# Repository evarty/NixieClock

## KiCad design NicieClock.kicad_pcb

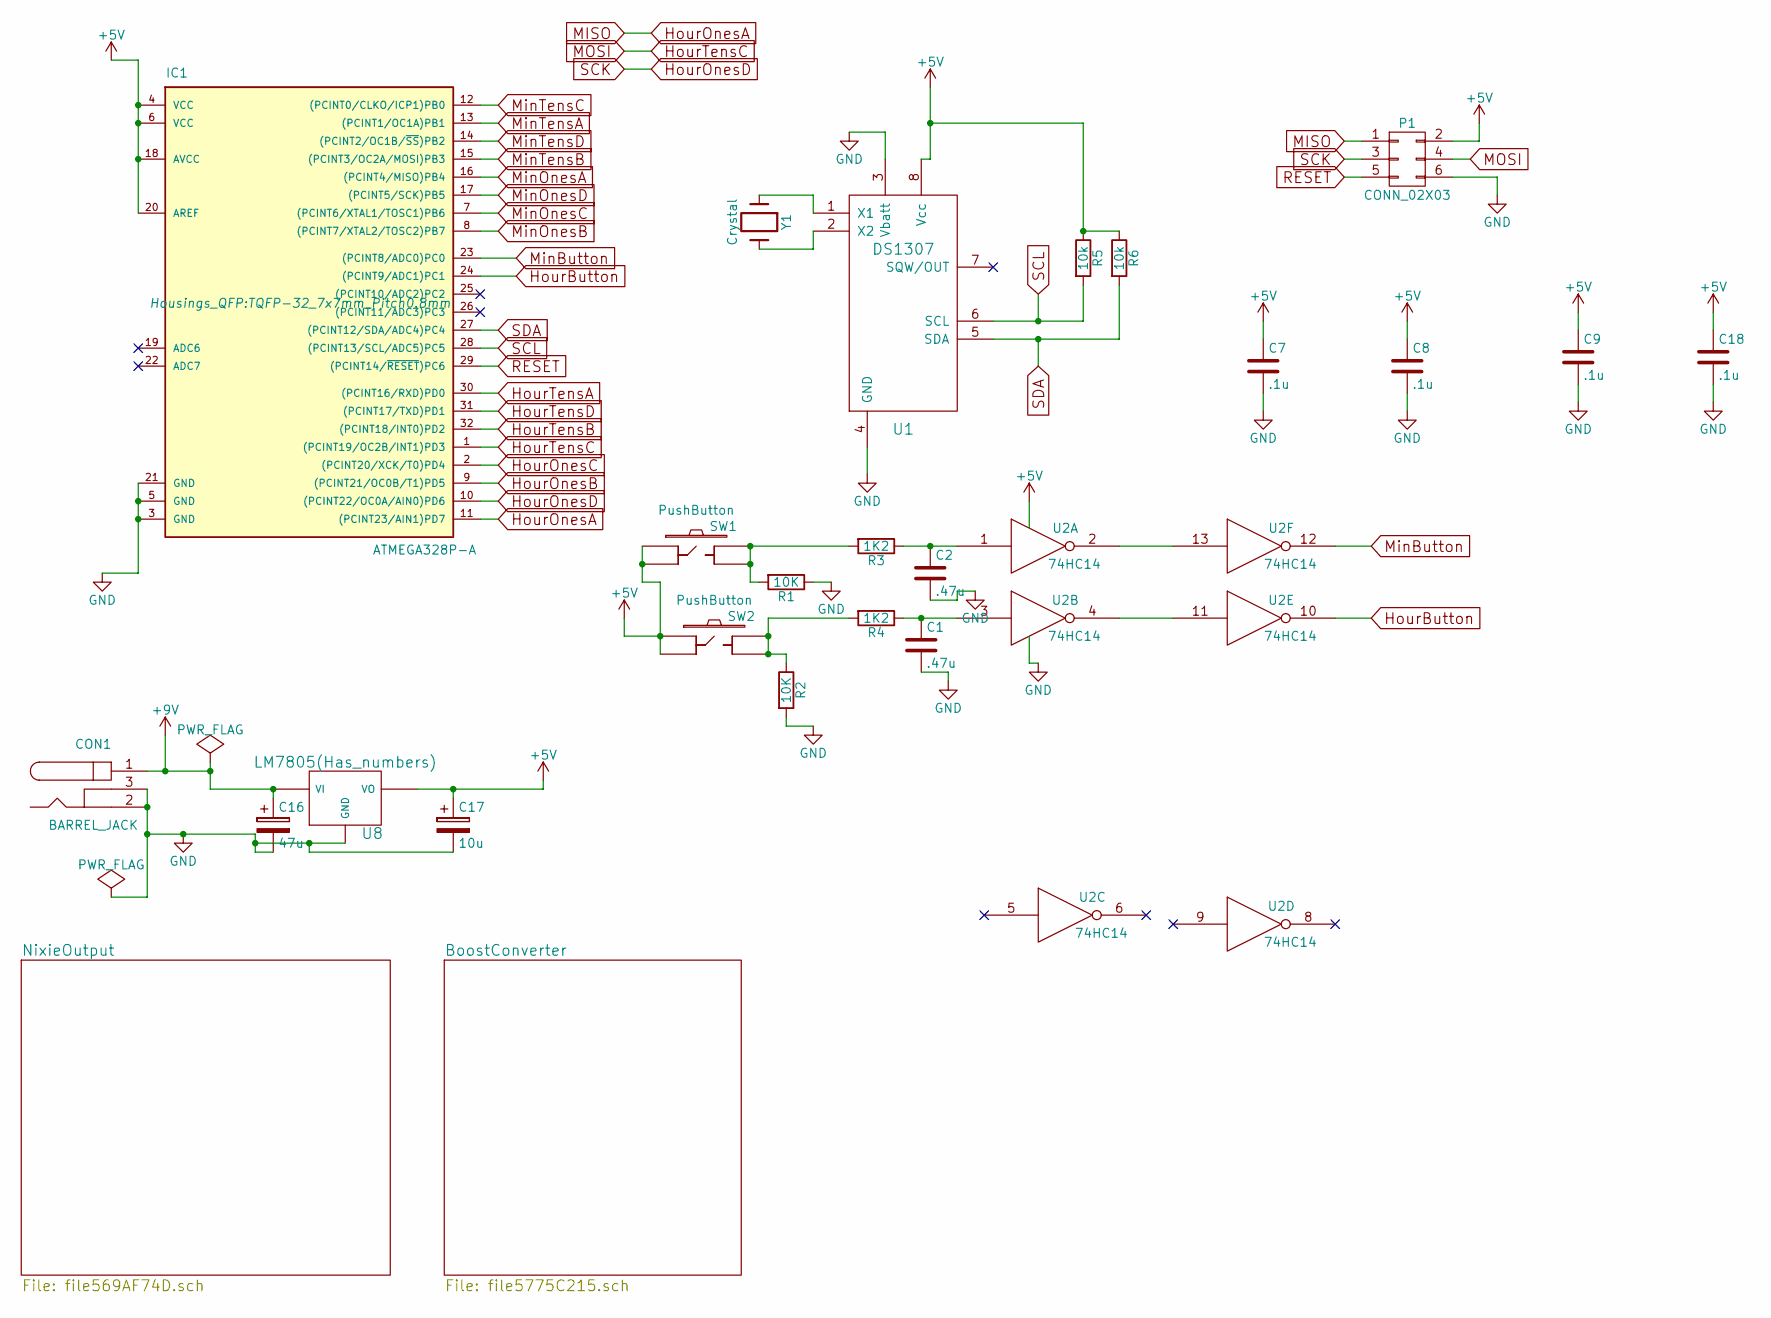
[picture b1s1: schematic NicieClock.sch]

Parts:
C1, C2: .47u; C_0805_HandSoldering
C7, C8, C9, C18: .1u; C_0805_HandSoldering
C16: 47u; C_Radial_D5_L6_P2.5
C17: 10u; C_Radial_D5_L6_P2.5
CON1: BARREL_JACK
IC1: ATMEGA328P-A; TQFP-32_7x7mm_Pitch0.8mm
P1: CONN_02X03; Pin_Header_Straight_2x03
R1, R2: 10K; R_0805_HandSoldering
R3, R4: 1K2; R_0805_HandSoldering
R5, R6: 10k; R_0805_HandSoldering
SW1, SW2: PushButton
U1: DS1307; SOIC-8_3.9x4.9mm_Pitch1.27mm
U2: 74HC14; SOIC-14_3.9x8.7mm_Pitch1.27mm
U8: LM7805(Has_numbers); TO-220_Neutral123_Vertical
Y1: Crystal; SMDCrystal

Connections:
+5V: C7.1, C8.1, C9.1, C17.1, C18.1, IC1.4 (VCC), IC1.6 (VCC), IC1.18 (AVCC), IC1.20 (AREF), P1.2, R5.1, R6.1, SW1.1, SW1.4, SW2.1, SW2.4, U1.8 (Vcc), U2.14 (VCC), U8.3 (VO); also elsewhere on the board
+9V: C16.1, CON1.1, U8.1 (VI); also elsewhere on the board
GND: C1.2, C2.2, C7.2, C8.2, C9.2, C16.2, C17.2, C18.2, CON1.2, CON1.3, IC1.3 (GND), IC1.5 (GND), IC1.21 (GND), P1.6, R1.1, R2.2, U1.3 (Vbatt), U1.4 (GND), U2.7 (GND), U8.2 (GND); also elsewhere on the board
HourButton: IC1.24 ((PCINT9/ADC1)PC1), U2.10
HourOnesA: IC1.11 ((PCINT23/AIN1)PD7), P1.1; also elsewhere on the board
HourOnesB: IC1.9 ((PCINT21/OC0B/T1)PD5); also elsewhere on the board
HourOnesC: IC1.2 ((PCINT20/XCK/T0)PD4); also elsewhere on the board
HourOnesD: IC1.10 ((PCINT22/OC0A/AIN0)PD6), P1.3; also elsewhere on the board
HourTensA: IC1.30 ((PCINT16/RXD)PD0); also elsewhere on the board
HourTensB: IC1.32 ((PCINT18/INT0)PD2); also elsewhere on the board
HourTensC: IC1.1 ((PCINT19/OC2B/INT1)PD3), P1.4; also elsewhere on the board
HourTensD: IC1.31 ((PCINT17/TXD)PD1); also elsewhere on the board
MinButton: IC1.23 ((PCINT8/ADC0)PC0), U2.12
MinOnesA: IC1.16 ((PCINT4/MISO)PB4); also elsewhere on the board
MinOnesB: IC1.8 ((PCINT7/XTAL2/TOSC2)PB7); also elsewhere on the board
MinOnesC: IC1.7 ((PCINT6/XTAL1/TOSC1)PB6); also elsewhere on the board
MinOnesD: IC1.17 ((PCINT5/SCK)PB5); also elsewhere on the board
MinTensA: IC1.13 ((PCINT1/OC1A)PB1); also elsewhere on the board
MinTensB: IC1.15 ((PCINT3/OC2A/MOSI)PB3); also elsewhere on the board
MinTensC: IC1.12 ((PCINT0/CLKO/ICP1)PB0); also elsewhere on the board
MinTensD: IC1.14 ((PCINT2/OC1B/~SS~)PB2); also elsewhere on the board
unnamed: C1.1, R4.1, U2.3
unnamed: C2.1, R3.1, U2.1
unnamed: R1.2, R3.2, SW1.2, SW1.3
unnamed: R2.1, R4.2, SW2.2, SW2.3
unnamed: U1.1 (X1), Y1.1
unnamed: U1.2 (X2), Y1.2
unnamed: U2.4, U2.11
unnamed: U2.2, U2.13
RESET: IC1.29 ((PCINT14/~RESET~)PC6), P1.5
SCL: IC1.28 ((PCINT13/SCL/ADC5)PC5), R5.2, U1.6 (SCL)
SDA: IC1.27 ((PCINT12/SDA/ADC4)PC4), R6.2, U1.5 (SDA)

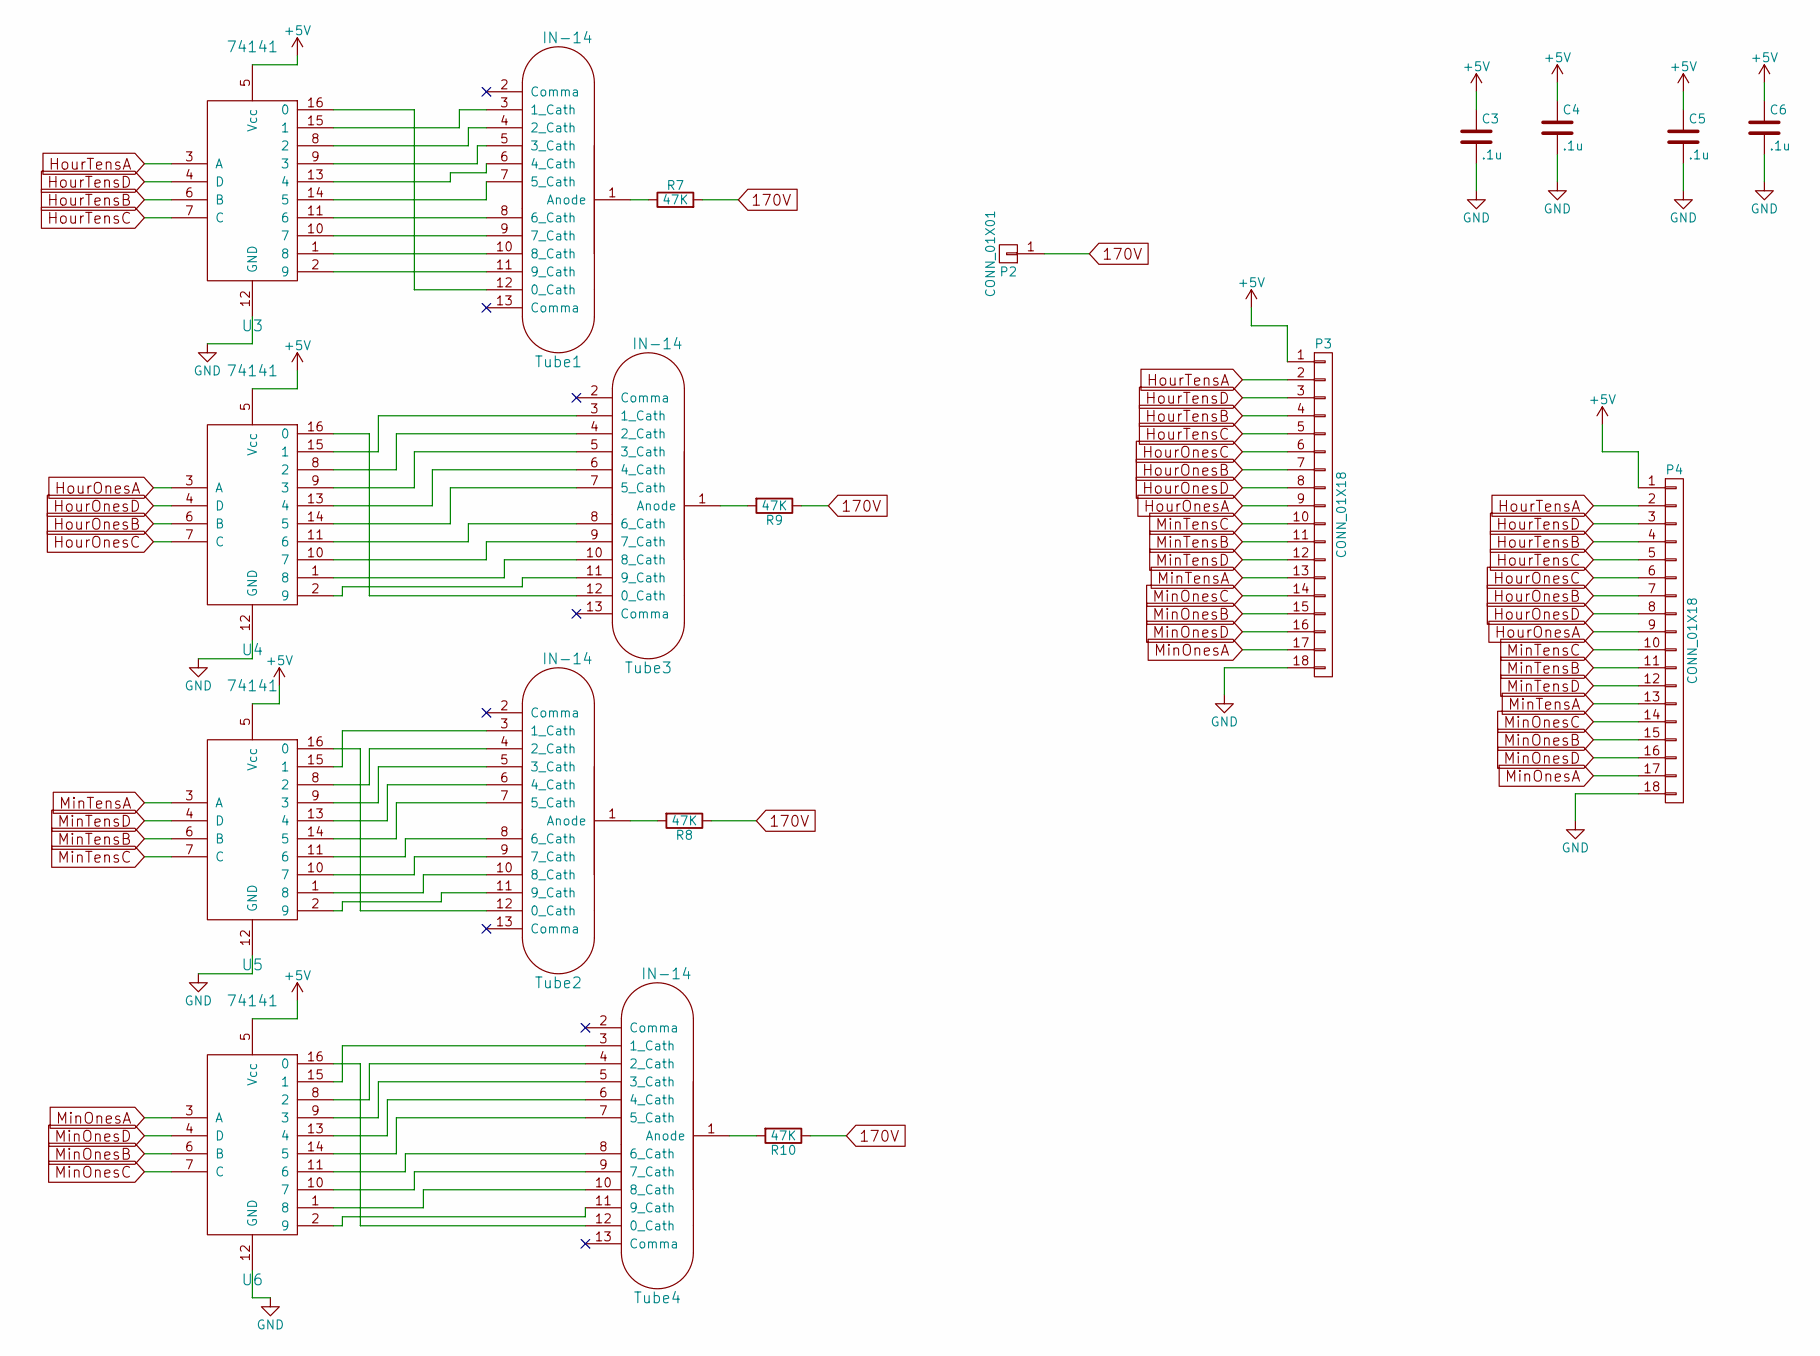
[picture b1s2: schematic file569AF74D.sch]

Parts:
C3, C4, C5, C6: .1u; C_0805_HandSoldering
P2: CONN_01X01; Pin_Header_Straight_1x01
P3, P4: CONN_01X18; Pin_Header_Straight_1x18
R7, R8, R9, R10: 47K; R_1206_HandSoldering
Tube1, Tube2, Tube3, Tube4: IN-14
U3, U4, U5, U6: 74141; DIP-16_W7.62mm_LongPads

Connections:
170V: P2.1, R7.2, R8.1, R9.1, R10.1; also elsewhere on the board
+5V: C3.1, C4.1, C5.1, C6.1, P3.1, P4.1, U3.5 (Vcc), U4.5 (Vcc), U5.5 (Vcc), U6.5 (Vcc); also elsewhere on the board
GND: C3.2, C4.2, C5.2, C6.2, P3.18, P4.18, U3.12 (GND), U4.12 (GND), U5.12 (GND), U6.12 (GND); also elsewhere on the board
HourOnesA: P3.9, P4.9, U4.3 (A); also elsewhere on the board
HourOnesB: P3.7, P4.7, U4.6 (B); also elsewhere on the board
HourOnesC: P3.6, P4.6, U4.7 (C); also elsewhere on the board
HourOnesD: P3.8, P4.8, U4.4 (D); also elsewhere on the board
HourTensA: P3.2, P4.2, U3.3 (A); also elsewhere on the board
HourTensB: P3.4, P4.4, U3.6 (B); also elsewhere on the board
HourTensC: P3.5, P4.5, U3.7 (C); also elsewhere on the board
HourTensD: P3.3, P4.3, U3.4 (D); also elsewhere on the board
MinOnesA: P3.17, P4.17, U6.3 (A); also elsewhere on the board
MinOnesB: P3.15, P4.15, U6.6 (B); also elsewhere on the board
MinOnesC: P3.14, P4.14, U6.7 (C); also elsewhere on the board
MinOnesD: P3.16, P4.16, U6.4 (D); also elsewhere on the board
MinTensA: P3.13, P4.13, U5.3 (A); also elsewhere on the board
MinTensB: P3.11, P4.11, U5.6 (B); also elsewhere on the board
MinTensC: P3.10, P4.10, U5.7 (C); also elsewhere on the board
MinTensD: P3.12, P4.12, U5.4 (D); also elsewhere on the board
unnamed: R7.1, Tube1.1 (Anode)
unnamed: R8.2, Tube2.1 (Anode)
unnamed: R9.2, Tube3.1 (Anode)
unnamed: R10.2, Tube4.1 (Anode)
unnamed: Tube1.3 (1_Cath), U3.15 (1)
unnamed: Tube1.4 (2_Cath), U3.8 (2)
unnamed: Tube1.5 (3_Cath), U3.9 (3)
unnamed: Tube1.6 (4_Cath), U3.13 (4)
unnamed: Tube1.7 (5_Cath), U3.14 (5)
unnamed: Tube1.8 (6_Cath), U3.11 (6)
unnamed: Tube1.9 (7_Cath), U3.10 (7)
unnamed: Tube1.10 (8_Cath), U3.1 (8)
unnamed: Tube1.11 (9_Cath), U3.2 (9)
unnamed: Tube1.12 (0_Cath), U3.16 (0)
unnamed: Tube2.3 (1_Cath), U5.15 (1)
unnamed: Tube2.4 (2_Cath), U5.8 (2)
unnamed: Tube2.5 (3_Cath), U5.9 (3)
unnamed: Tube2.6 (4_Cath), U5.13 (4)
unnamed: Tube2.7 (5_Cath), U5.14 (5)
unnamed: Tube2.8 (6_Cath), U5.11 (6)
unnamed: Tube2.9 (7_Cath), U5.10 (7)
unnamed: Tube2.10 (8_Cath), U5.1 (8)
unnamed: Tube2.11 (9_Cath), U5.2 (9)
unnamed: Tube2.12 (0_Cath), U5.16 (0)
unnamed: Tube3.3 (1_Cath), U4.15 (1)
unnamed: Tube3.4 (2_Cath), U4.8 (2)
unnamed: Tube3.5 (3_Cath), U4.9 (3)
unnamed: Tube3.6 (4_Cath), U4.13 (4)
unnamed: Tube3.7 (5_Cath), U4.14 (5)
unnamed: Tube3.8 (6_Cath), U4.11 (6)
unnamed: Tube3.9 (7_Cath), U4.10 (7)
unnamed: Tube3.10 (8_Cath), U4.1 (8)
unnamed: Tube3.11 (9_Cath), U4.2 (9)
unnamed: Tube3.12 (0_Cath), U4.16 (0)
unnamed: Tube4.3 (1_Cath), U6.15 (1)
unnamed: Tube4.4 (2_Cath), U6.8 (2)
unnamed: Tube4.5 (3_Cath), U6.9 (3)
unnamed: Tube4.6 (4_Cath), U6.13 (4)
unnamed: Tube4.7 (5_Cath), U6.14 (5)
unnamed: Tube4.8 (6_Cath), U6.11 (6)
unnamed: Tube4.9 (7_Cath), U6.10 (7)
unnamed: Tube4.10 (8_Cath), U6.1 (8)
unnamed: Tube4.11 (9_Cath), U6.2 (9)
unnamed: Tube4.12 (0_Cath), U6.16 (0)

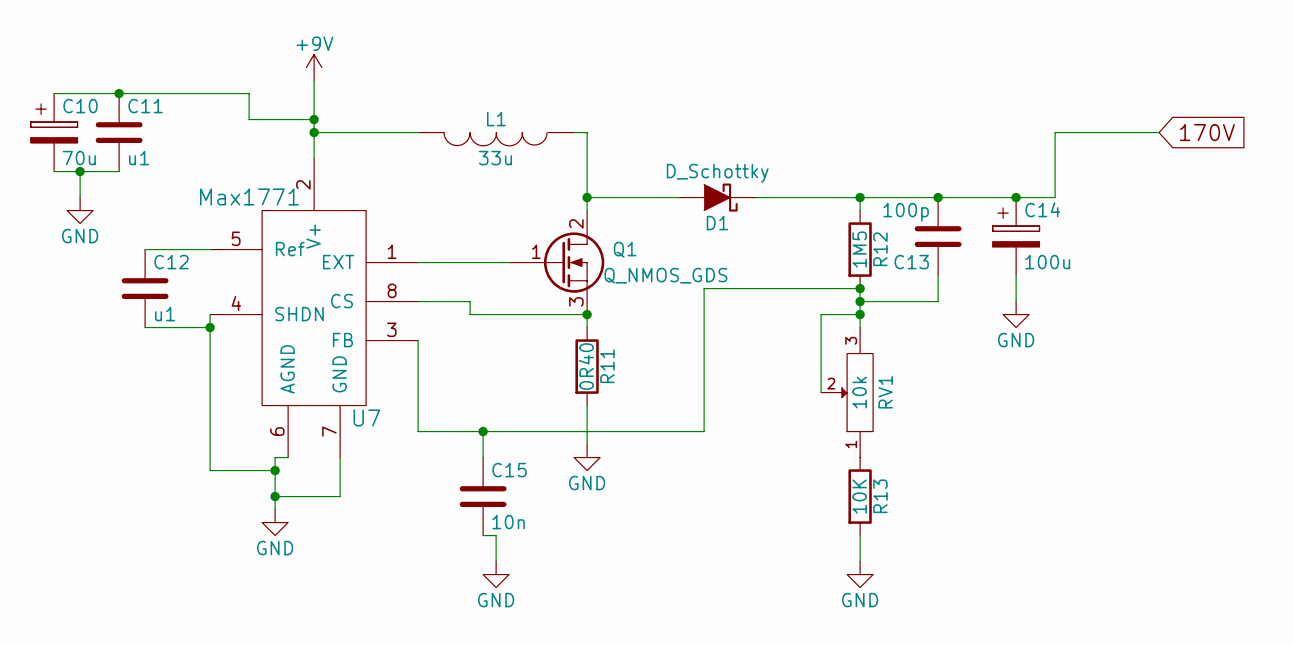
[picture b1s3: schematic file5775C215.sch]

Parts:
C10: 70u; c_elec_6.3x5.3
C11, C12: u1; C_0805_HandSoldering
C13: 100p; C_0805_HandSoldering
C14: 100u; SMDCap18mm
C15: 10n; C_0805_HandSoldering
D1: D_Schottky; SMB_Handsoldering
L1: 33u; Choke_SMD_10.4x10.4_H4.8
Q1: Q_NMOS_GDS; TO-252-2Lead
R11: 0R40; R_1206_HandSoldering
R12: 1M5; R_1206_HandSoldering
R13: 10K; R_0805_HandSoldering
RV1: 10k; EVM3Y
U7: Max1771; SOIC-8_3.9x4.9mm_Pitch1.27mm

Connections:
170V: C13.2, C14.1, D1.1 (K), R12.1; also elsewhere on the board
+9V: C10.1, C11.1, L1.2, U7.2 (V+); also elsewhere on the board
GND: C10.2, C11.2, C12.2, C14.2, C15.2, R11.2, R13.2, U7.4 (SHDN), U7.6 (AGND), U7.7 (GND); also elsewhere on the board
unnamed: C12.1, U7.5 (Ref)
unnamed: C13.1, C15.1, R12.2, RV1.2, RV1.3, U7.3 (FB)
unnamed: D1.2 (A), L1.1, Q1.2 (D)
unnamed: Q1.1 (G), U7.1 (EXT)
unnamed: Q1.3 (S), R11.1, U7.8 (CS)
unnamed: R13.1, RV1.1

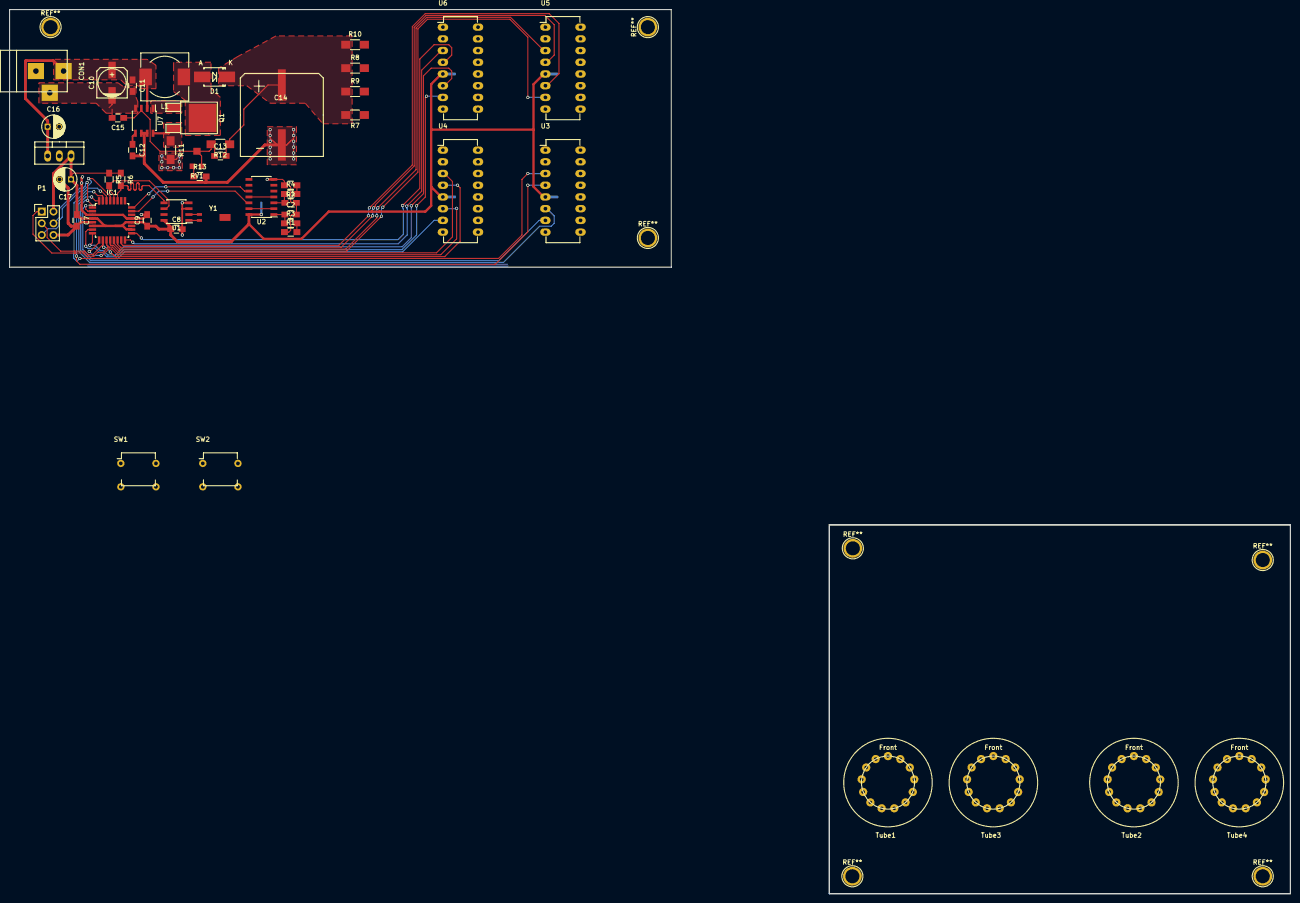
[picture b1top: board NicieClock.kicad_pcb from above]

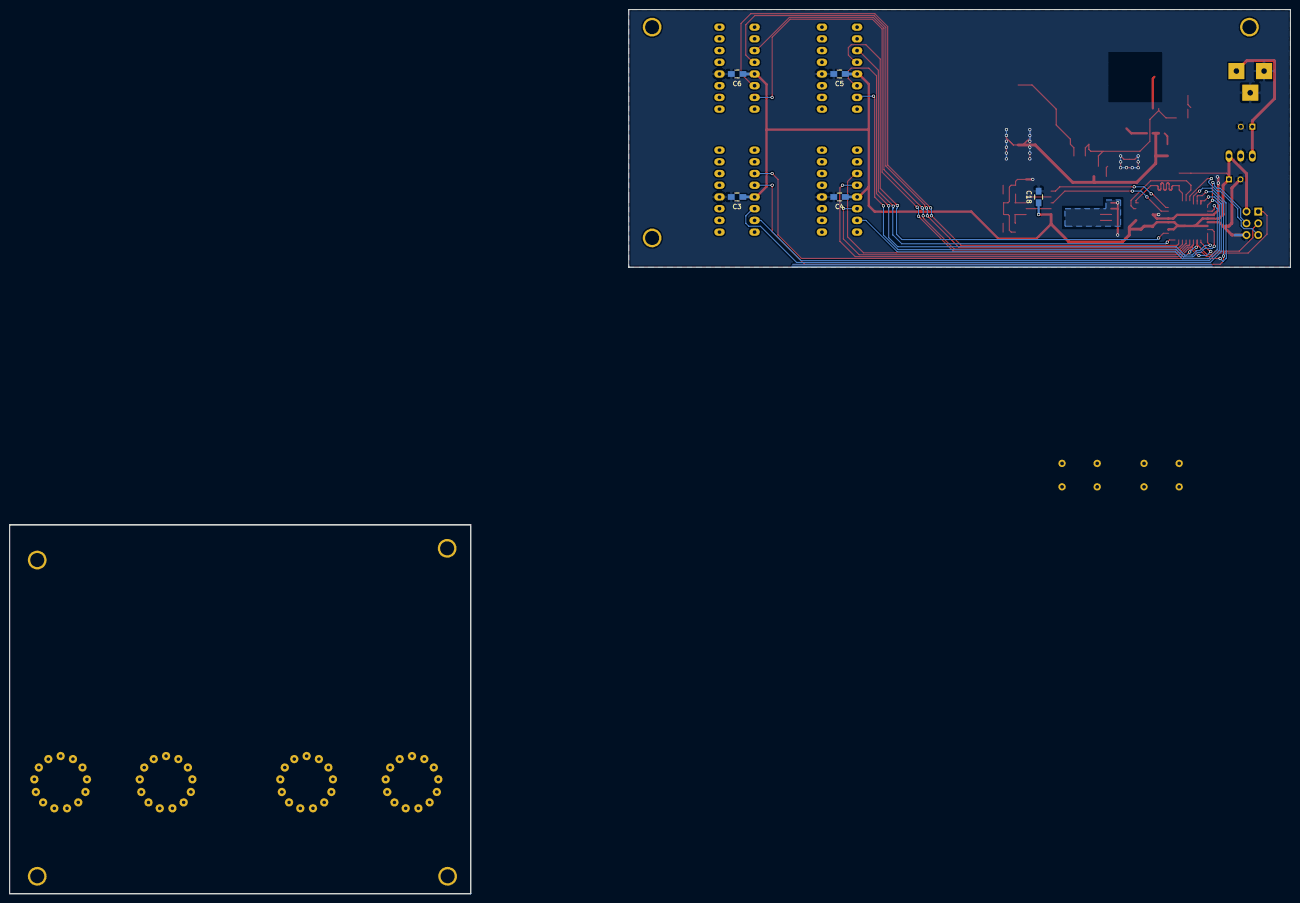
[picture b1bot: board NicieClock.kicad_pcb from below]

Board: 2 copper layers, 143.5 x 55.9 mm, 53 parts (5 on the bottom side), 83 nets.

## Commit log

2016-07-15 Added files
2016-07-15 isolated boost converter
